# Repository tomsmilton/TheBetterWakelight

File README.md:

# TheBetterWakelight

Two independent takes on the same idea: an **ESP32-based DMX sunrise
controller for the Neewer PL60C**. The ESP32 plugs into the lamp's 5-pin
DMX port and ramps it from black to full daylight before your alarm,
configured from a phone-friendly web portal on your home Wi-Fi.

```
phone ──WiFi──▶ ESP32 ──DMX-512──▶ Neewer PL60C
        http://wakelight.local/
```

Each version is fully self-contained in its own folder — separate firmware,
docs and build setup. Pick whichever you want to build.

## [`v1-dmx-wakelight/`](v1-dmx-wakelight/) — the original build

The first working version. ESP-IDF / PlatformIO firmware that drives the
PL60C over DMX-512 on a configurable, **waypoint-based** sunrise ramp, with a
mobile web UI for schedule setup and real-time control. Mixes interpolated
brightness/colour-temperature waypoints with the PL60C's 17 named special
effects. Includes wiring schematics and helper scripts.

→ [Read the v1 README](v1-dmx-wakelight/README.md)

## [`v2-better-wakelight/`](v2-better-wakelight/) — the better wakelight

The refined product. A purpose-built **custom PCB** (Neutrik 5-pin XLR,
USB-C power, CH340C one-click flashing, THVD1410 RS-485 output stage) plus
firmware and a Wi-Fi setup portal. Ships hardware deliverables — KiCad
project, gerbers, schematics and JLCPCB order files (BOM + pick-and-place).

| Custom PCB — XLR variant (top) | Bottom |
|:---:|:---:|
|  |  |

→ [Read the v2 README](v2-better-wakelight/README.md) ·
[original project brief](v2-better-wakelight/BRIEF.md)

---

Build artifacts (PlatformIO/ESP-IDF output, KiCad caches, generated meshes,
Wi-Fi secrets) are gitignored per-folder.

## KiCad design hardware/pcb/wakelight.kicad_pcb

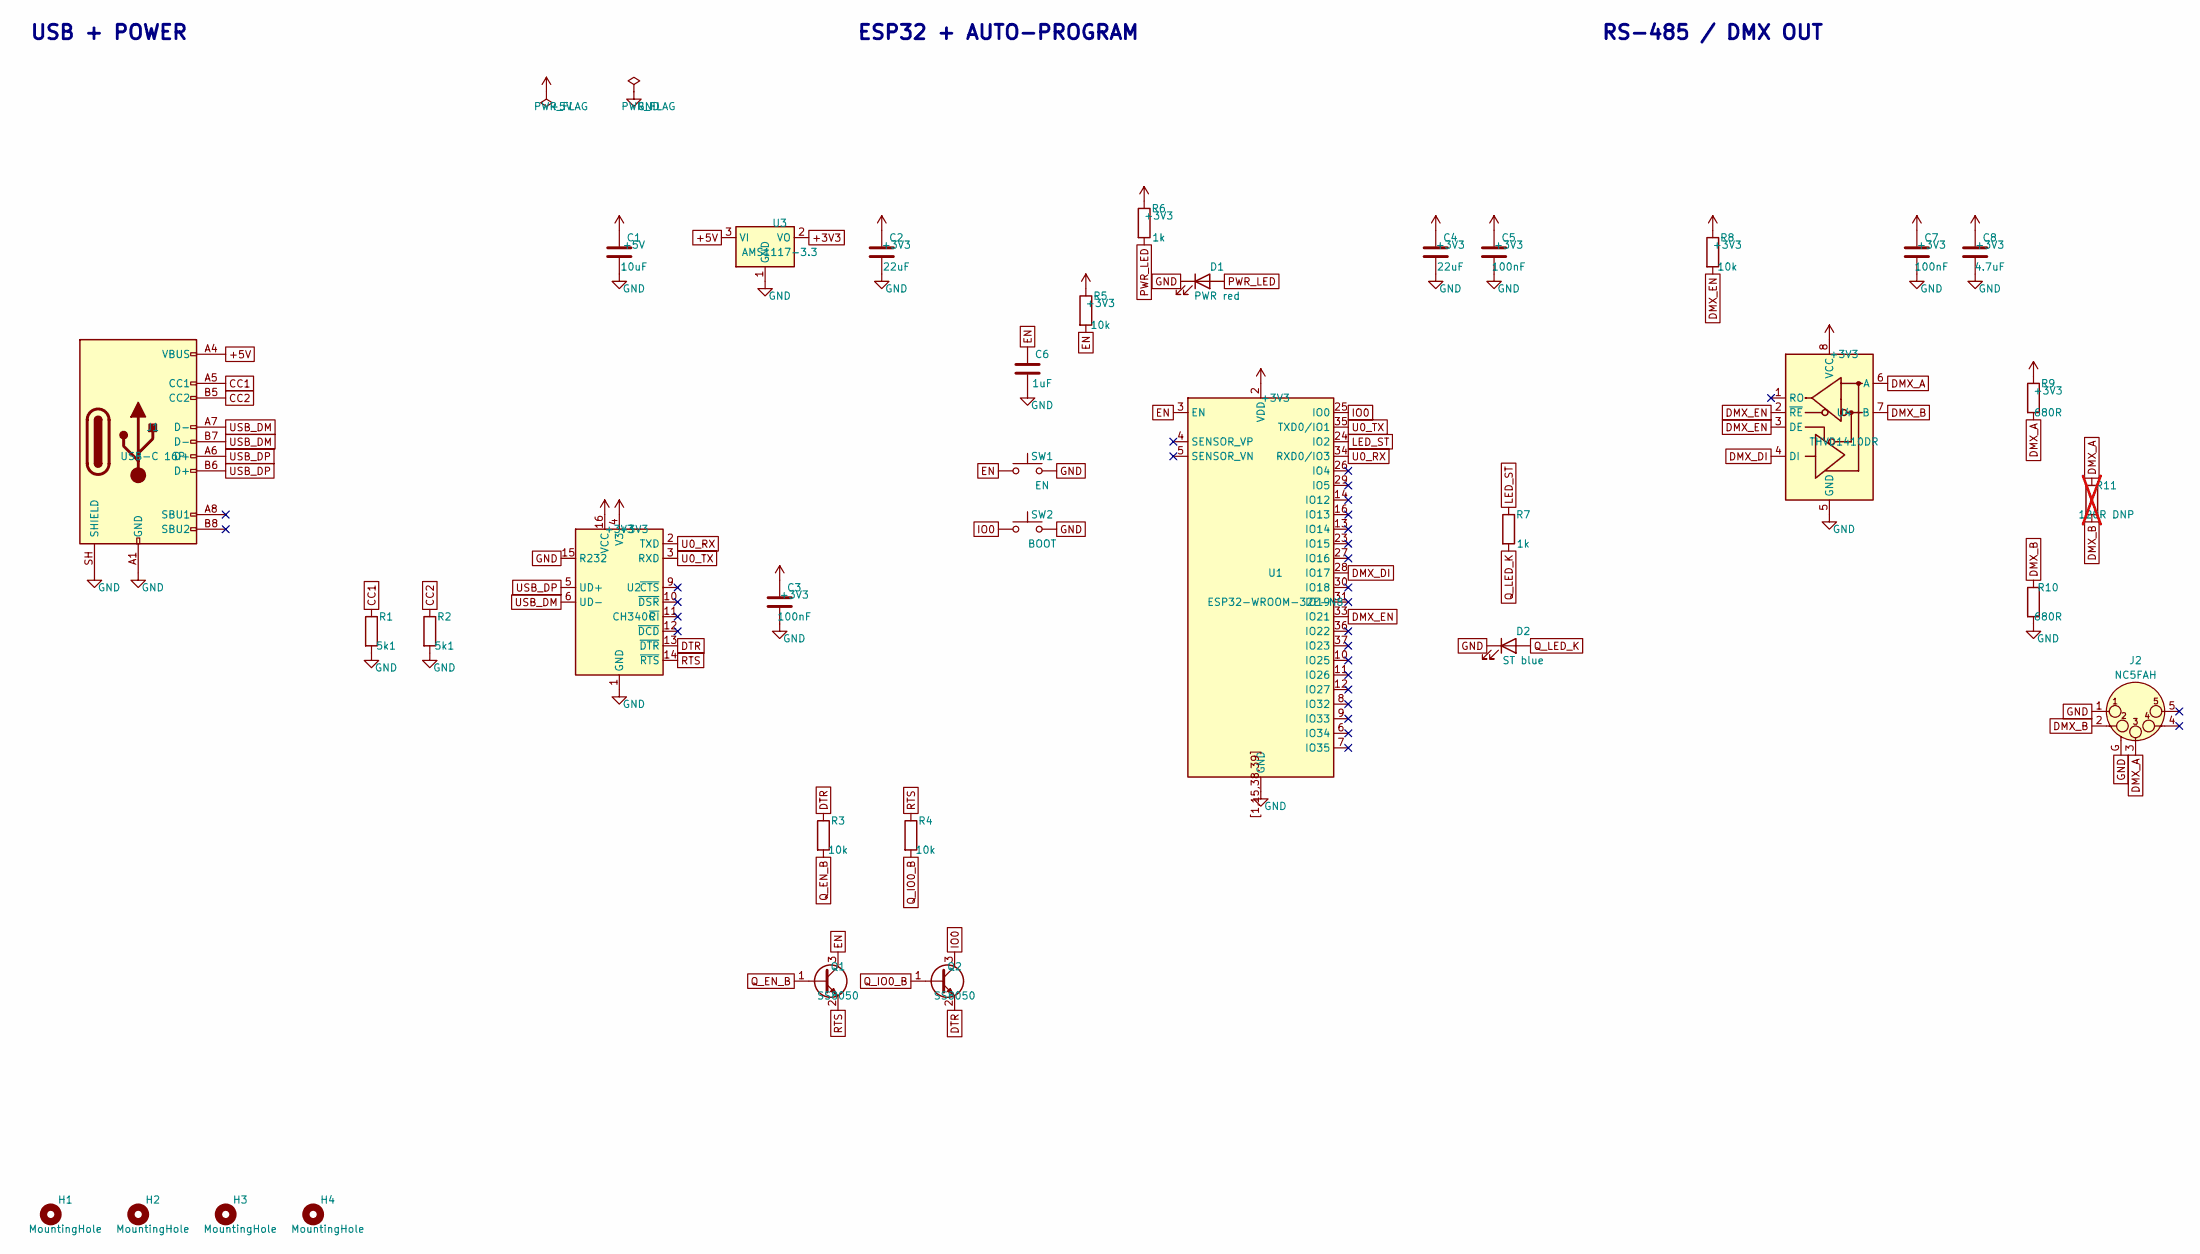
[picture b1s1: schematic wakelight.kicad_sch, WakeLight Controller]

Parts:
C1: 10uF; C_0805_2012Metric
C2, C4: 22uF; C_0805_2012Metric
C3, C5, C7: 100nF; C_0603_1608Metric
C6: 1uF; C_0603_1608Metric
C8: 4.7uF; C_0805_2012Metric
D1: PWR red; LED_0603_1608Metric
D2: ST blue; LED_0603_1608Metric
H1, H2, H3, H4: MountingHole; MountingHole_3.2mm_M3
J1: USB-C 16P; USB_C_Receptacle_HRO_TYPE-C-31-M-12
J2: NC5FAH; Jack_XLR_Neutrik_NC5FAH_Horizontal
Q1, Q2: SS8050; SOT-23
R1, R2: 5k1; R_0603_1608Metric
R3, R4, R5, R8: 10k; R_0603_1608Metric
R6, R7: 1k; R_0603_1608Metric
R9, R10: 680R; R_0603_1608Metric
R11: 120R DNP; R_0603_1608Metric; not fitted
SW1: EN; SW_SPST_TL3342
SW2: BOOT; SW_SPST_TL3342
U1: ESP32-WROOM-32E-N8; ESP32-WROOM-32E
U2: CH340C; SOIC-16_3.9x9.9mm_P1.27mm
U3: AMS1117-3.3; SOT-223-3_TabPin2
U4: THVD1410DR; SOIC-8_3.9x4.9mm_P1.27mm

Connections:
+3V3: C2.1, C3.1, C4.1, C5.1, C7.1, C8.1, R5.1, R6.1, R8.1, R9.1, U1.2 (VDD), U2.4 (V3), U2.16 (VCC), U3.2 (VO), U4.8 (VCC)
+5V: C1.1, J1.A4 (VBUS), J1.A9 (VBUS), J1.B4 (VBUS), J1.B9 (VBUS), U3.3 (VI)
CC1: J1.A5 (CC1), R1.1
CC2: J1.B5 (CC2), R2.1
DMX_A: J2.3, R9.2, R11.1, U4.6 (A)
DMX_B: J2.2, R10.1, R11.2, U4.7 (B)
DMX_DI: U1.28 (IO17), U4.4 (DI)
DMX_EN: R8.2, U1.33 (IO21), U4.2 (~RE), U4.3 (DE)
DTR: Q2.2 (E), R3.1, U2.13 (~DTR)
EN: C6.1, Q1.3 (C), R5.2, SW1.1, U1.3 (EN)
GND: C1.2, C2.2, C3.2, C4.2, C5.2, C6.2, C7.2, C8.2, D1.1 (K), D2.1 (K), J1.A1 (GND), J1.A12 (GND), J1.B1 (GND), J1.B12 (GND), J1.SH (SHIELD), J2.1, J2.G, R1.2, R2.2, R10.2, SW1.2, SW2.2, U1.1, U1.15, U1.38, U1.39, U1.[1,15,38,39] (GND), U2.1 (GND), U2.15 (R232), U3.1 (GND), U4.5 (GND)
IO0: Q2.3 (C), SW2.1, U1.25 (IO0)
LED_ST: R7.1, U1.24 (IO2)
PWR_LED: D1.2 (A), R6.2
Q_EN_B: Q1.1 (B), R3.2
Q_IO0_B: Q2.1 (B), R4.2
Q_LED_K: D2.2 (A), R7.2
RTS: Q1.2 (E), R4.1, U2.14 (~RTS)
U0_RX: U1.34 (RXD0/IO3), U2.2 (TXD)
U0_TX: U1.35 (TXD0/IO1), U2.3 (RXD)
USB_DM: J1.A7 (D-), J1.B7 (D-), U2.6 (UD-)
USB_DP: J1.A6 (D+), J1.B6 (D+), U2.5 (UD+)

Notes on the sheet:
USB + POWER
ESP32 + AUTO-PROGRAM
RS-485 / DMX OUT

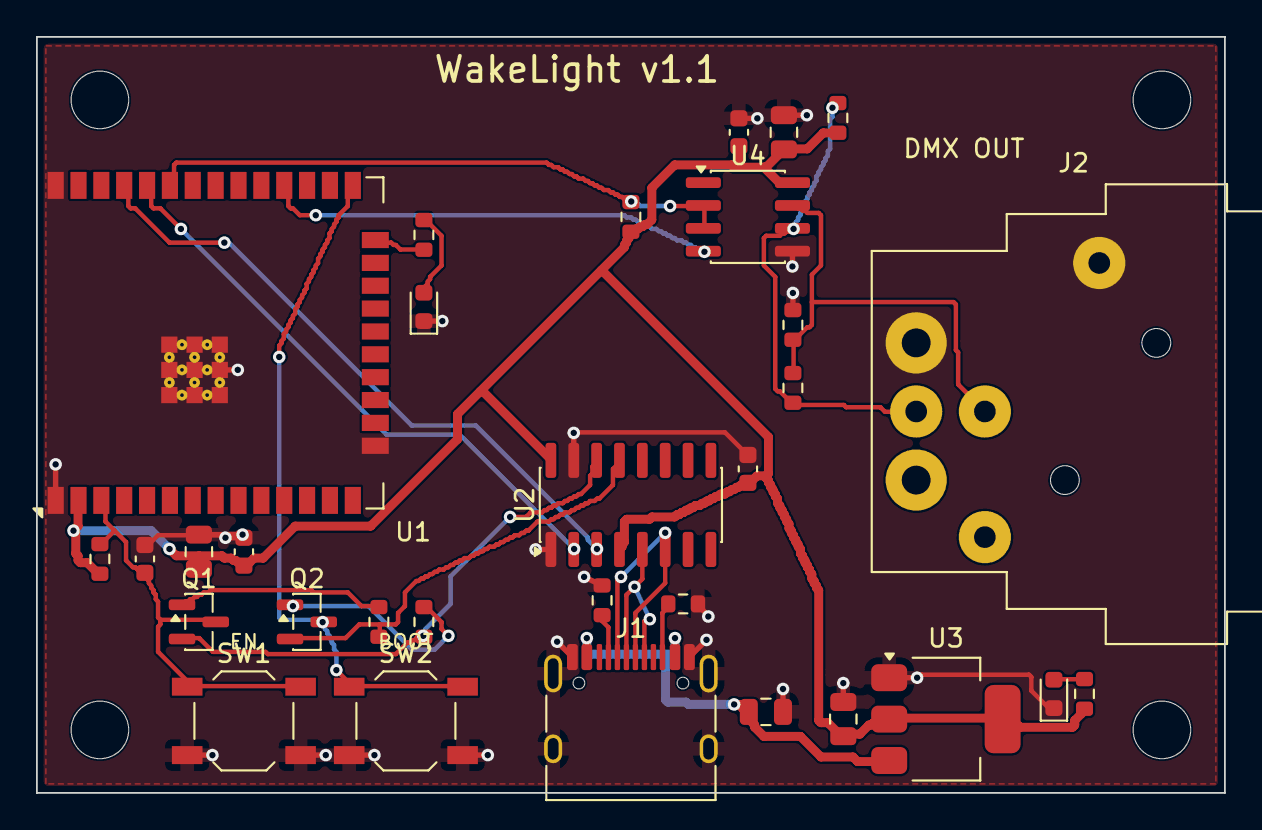
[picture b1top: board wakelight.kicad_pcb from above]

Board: 2 copper layers, 66.0 x 42.0 mm, 35 parts (0 on the bottom side), 22 nets.

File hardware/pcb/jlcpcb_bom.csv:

Comment,Designator,Footprint,LCSC Part #
10k 0603,"R8,R4,R5,R3",R_0603_1608Metric,C25804
100nF 0603,"C5,C7,C3",C_0603_1608Metric,C14663
Blue LED 0603 KT-0603B,D2,LED_0603_1608Metric,C2288
THVD1410DR,U4,SOIC-8_3.9x4.9mm_P1.27mm,C2671345
680R 0603,"R10,R9",R_0603_1608Metric,C23228
1uF 0603,C6,C_0603_1608Metric,C15849
USB-C 16P TYPE-C-31-M-12,J1,USB_C_Receptacle_HRO_TYPE-C-31-M-12,C165948
SS8050,"Q1,Q2",SOT-23,C2150
Red LED 0603,D1,LED_0603_1608Metric,C2286
10uF 0805,C1,C_0805_2012Metric,C15850
ESP32-WROOM-32E-N8,U1,ESP32-WROOM-32E,C701342
5.1k 0603,"R2,R1",R_0603_1608Metric,C23186
22uF 0805,"C2,C4",C_0805_2012Metric,C45783
4.7uF 0805,C8,C_0805_2012Metric,C1779
Tact switch TS-1187A,"SW1,SW2",SW_SPST_TL3342,C318884
AMS1117-3.3,U3,SOT-223-3_TabPin2,C6186
CH340C,U2,SOIC-16_3.9x9.9mm_P1.27mm,C84681
1k 0603,"R7,R6",R_0603_1608Metric,C21190
